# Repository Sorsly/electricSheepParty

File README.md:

# esp
Our senior design project, Electronic Sheep Party.
## Steps to Run
* Turn on LAN (Make sure all bots are configured to connect)
* Set up camera above the bots
* power cycle each bot and wait for the green light to turn off
* run `putilov getIP`, wait
* run `putilov run`, select y
* Launch your two seprate game front ends
* play game

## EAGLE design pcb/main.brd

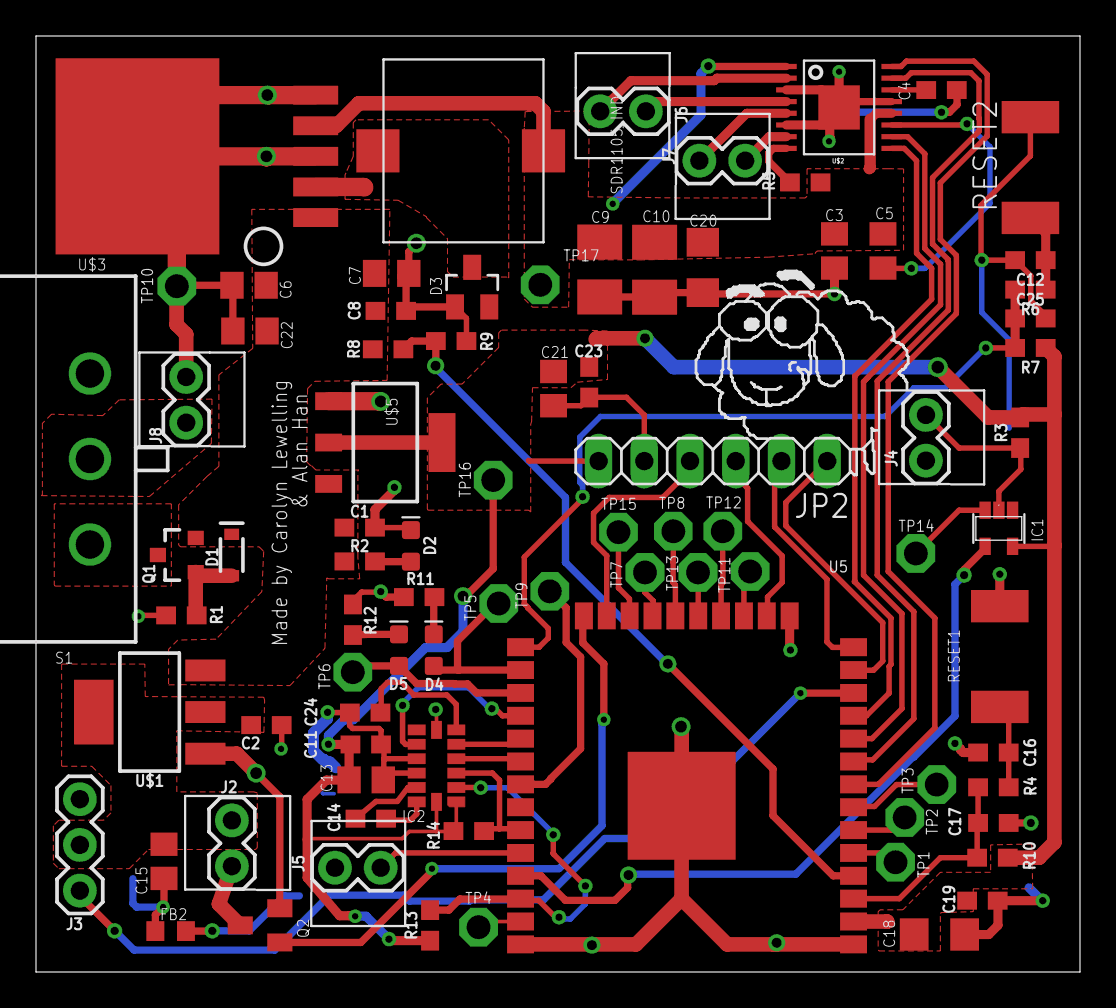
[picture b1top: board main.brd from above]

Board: 2 copper layers, 58.0 x 52.0 mm, 85 parts (0 on the bottom side), 60 nets.

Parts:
C1, C2, C8, C11, C23: 0.1uF; 0603
C3, C5, C7, C13, C15, C21, C22: 10uF; C0805
C4: 2.2uF; C0603
C6: 22uF; C0805
C9, C10: 220uF; B/3528-21R
C12, C16, C17, C25: 1nF; 0603
C14: 0.22uF; 0603
C18, C20: 100uF; C1206
C19: 1uF; 0603
C24: 4.7uF; 0603
D1: 250mA/100V; SOD-323
D2: LED-0603
D3: BAT54; SOT23
D4: red; LED-0603
D5: green; LED-0603
FB2: R0603
FRAME1, FRAME2: FRAME-LETTERNO_PACKAGE; DUMMY
IC1: NC7SZ14M5X; SOT23-5
IC2: LSM303DLHC; LGA-14
J2, J4, J5, J8: 1X02
J3: 455-1750-1-ND; 1X03
J6: M1 connector; 1X02
J7: M2 connector; 1X02
JP2: 1X06
Q1: 2.5A/30V/105mΩ; SOT23-3
Q2: SOT23
R1: 100k; 0603
R2, R11, R12: 330; 0603
R3: 8.2k; 0603
R4, R6, R7, R10: 470; 0603
R5, R13, R14: 10k; 0603
R8: 2k; 0603
R9: 1k; 0603
RESET1, RESET2: S2; SW_2512
S1: L102021ML04Q
TP1, TP2, TP3, TP4, TP5, TP6, TP7, TP8, TP9, TP10, TP11, TP12, TP13, TP14, TP15, TP16, TP17: TPPAD1-13; P1-13
U5: ESP-WROOM-32
U$1: AZ1117E; SOT223
U$2: DRV8833C; HTSSOP-16
U$3: AP1506; TO263-5
U$4: SDR1105_IND; SDR1105
U$5: SC1202-3.3V; SOT-223

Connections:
1/3_BAT: R8.1, R9.2, U5.4
3V3: C11.1, C13.1, C18.1, C19.1, C21.1, C23.1, IC1.5, IC2.1, IC2.14, JP2.6, R3.2, R7.1, R10.1, R13.1, R14.1, TP16.TP, U5.2, U$5.2, U$5.TAB
3V3M: C3.1, C5.1, C9.+, C10.+, C20.1, R5.2, TP17.TP, U$2.1, U$2.12, U$3.4, U$4.P$2
5V: C2.1, C15.2, J2.2, J3.2, U$1.2, U$1.4
6V: C1.1, C6.1, C7.1, C8.1, C22.1, D1.C, Q1.2, R2.2, R8.2, U$1.3, U$3.1, U$5.3
6V_RAW: J8.1, S1.P$2
ADC_PHOTO: IC1.2, J4.2, R3.1
AGND: C1.2, C2.2, C3.2, C4.2, C6.2, C7.2, C8.2, C9.-, C10.-, C15.1, C20.2, C22.2, D2.C, D3.1, FB2.1, J3.3, J8.2, Q2.2, R1.1, R9.1, TP10.TP, U$1.1, U$2.3, U$2.6, U$2.13, U$2.17, U$3.3, U$3.5, U$3.6, U$5.1
DAT_RDY: IC2.9, U5.28
EN: C17.1, R4.2, R10.2, U5.3
GND: C11.2, C12.2, C13.2, C16.2, C17.2, C18.2, C19.2, C21.2, C23.2, C24.2, C25.2, FB2.2, IC1.3, IC2.7, IC2.10, IC2.11, J4.1, J5.1, JP2.5, R11.1, R12.1, RESET1.2, RESET2.2, TP14.TP, U5.1, U5.15, U5.38, U5.GND
INT1: IC2.5, U5.29
INT2: IC2.4, U5.30
IO0: C25.1, R6.2, R7.2, U5.25
M1+: J6.2, U$2.2
M1-: J6.1, U$2.4
M2+: J7.2, U$2.7
M2-: J7.1, U$2.5
unnamed: D1.A, Q1.1, R1.2
unnamed: D2.A, R2.1
unnamed: Q1.3, S1.P$3
unnamed: TP1.TP, U5.5
unnamed: TP2.TP, U5.6
unnamed: C12.1, R6.1, RESET2.1
unnamed: D3.3, U$3.2, U$4.P$1
unnamed: C4.1, U$2.14
unnamed: C5.2, U$2.11
unnamed: J2.1, Q2.3
unnamed: C16.1, R4.1, RESET1.1
unnamed: R5.1, U$2.8
unnamed: TP3.TP, U5.7
unnamed: TP8.TP, U5.20
unnamed: D4.A, TP5.TP, U5.26
unnamed: TP7.TP, U5.21
unnamed: TP15.TP, U5.22
unnamed: D5.A, TP6.TP, U5.27
unnamed: TP11.TP, U5.17
unnamed: TP12.TP, U5.18
unnamed: TP13.TP, U5.19
unnamed: TP9.TP, U5.31
unnamed: TP4.TP, U5.37
unnamed: D4.C, R11.2
unnamed: D5.C, R12.2
unnamed: C14.2, IC2.13
unnamed: C14.1, IC2.12
unnamed: C24.1, IC2.6
PHOTO: IC1.4, U5.35
PWM_LASER: Q2.1, U5.24
PWM_LED: J5.2, U5.34
PWM_M1A: U5.8, U$2.16
PWM_M1B: U5.9, U$2.15
PWM_M2A: U5.11, U$2.9
PWM_M2B: U5.10, U$2.10
PWM_SERVO: J3.1, U5.12
SCL: IC2.2, R13.2, U5.36
SDA: IC2.3, R14.2, U5.33
TCK: JP2.3, U5.16
TDI: JP2.2, U5.14
TDO: JP2.4, U5.23
TMS: JP2.1, U5.13

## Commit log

2017-12-16 add gitignore + cvstuff
2017-12-16 adding cv install
2017-12-16 made and added some documentations
2017-12-23 UDP communication to bot working
2017-12-23 added move function
2018-01-10 adding devkitc sechematic
2018-01-12 stuff
2018-01-18 Build system working
2018-01-18 adding findip script
2018-01-21 added eagle files (sch and lbr)
2018-01-23 added H-bridge
2018-01-23 added more parts, found some parts, updated BOM with more info, reorganized schematic
2018-01-24 finished hbridge and buck converter
    created part for inductor, figured out values for buck converter caps,
    and wired hbridge
2018-01-24 updated hbridge
2018-01-24 added IMU
2018-01-26 changed gnd symbol (some weird 3.3v thing was happening) and added esp32
2018-01-27 added in new gnd symbols (doesn't default to 3.3v anymore); added in esp32 library
2018-01-29 Did IMU and most of UART
2018-01-29 initial pathfinder commit
2018-01-29 more progress
2018-01-30 works
2018-01-31 mosfet for laser
2018-01-31 wired up almost all of esp's peripherals
2018-01-31 updated project file (may have dropped electricSheepParty.lbr accidentally)
2018-02-02 progress
2018-02-02 message
2018-02-02 added putilov
2018-02-02 removing
2018-02-06 more esp pins and isolating grounds
2018-02-07 added schmitt trigger
2018-02-07 finished schematic (draft1)
2018-02-07 JTAG on Clion works
2018-02-07 putilov flashes correctlly
2018-02-08 layout done! (minus sheep image)
    Still need to add sheep and check with tolerances of wherever we fab at,
    but otherwise done!!!!
2018-02-09 added sheep
2018-02-10 fixed silkscreen (tPlace, tNames, tValues)
2018-02-14 added gerbers (oshPark.zip is the one that actually got sent to fab)
2018-02-14 built structure for control algorithm
2018-02-14 renaiming things
2018-02-21 mechanical (solidworks) files moved to repo
2018-02-21 began turret assm redesign, resized turret, added new cuts for: sg90 mount point, wires
2018-02-22 more mech stuff
2018-02-22 turret redesign done
2018-02-23 ui game
2018-02-24 finished battery cap
2018-02-25 command struct sent to bots
2018-02-25 completely finished assembly
    some bugs noticed:
    -wheel assembly has weird references to Assm1 or something like that
    -turret axis mate doesn't play well with other mates
2018-02-25 BOT COMMUNICATION WORKS BITCH, IM JUST AN IDIDOT
2018-02-25 datastructure commmunication working
2018-02-25 commenting + turret controlledover udp
2018-02-26 multiselect
2018-02-26 added colors and finished constraining final model; organized schematic
2018-02-27 fixes to battery holder, screw post adjustments for DC motor
2018-02-28 sch pdf generated
2018-02-28 the other pdf too
2018-03-04 converted battery holder to be detachable cantilevers (ie functional); (hopefully) toleranced turret bottom properly, need to confirm then will tolerance mid and top section (only need to tolerance p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
2018-03-07 all turret adjustments should be good, potentially need to shrink turret to fit within wheel clearance; made rest of body parts detacheable cantilevers
2018-03-08 batteryCant_01mm is actually a good pressfit when printed on T3 Land Factory in conjunction with female parts
2018-03-08 solidworks garbage collection
2018-03-09 editted part layouts. changed pins for uart
2018-03-10 communication
2018-03-11 guess I changed things?
2018-03-12 body is print ready with all fasteners
2018-03-12 CCCP ->Frontend comm
2018-03-13 CCCP->frontend dataparsing+ botmovement
2018-03-13 updating gitignore
2018-03-13 cleaning up clutter
2018-03-13 bringing in old working tracker
2018-03-14 hotfixes
2018-03-15 board JTAG programming working
2018-03-16 Frontend communication fully working
2018-03-16 comminting working frontend
2018-03-16 ok like i know this isnt the best practice but cut me some slack I have a couple branches going on
2018-03-17 periperals working
2018-03-19 camera to CCCP coded (untested)
2018-03-19 gofmt
2018-03-19 wheel fix
2018-03-19 misc
2018-03-20 fix for bodyTop turret wire slots
2018-03-20 changed IDing to hash tables
2018-03-20 in system software bot, camera, CCCP working
2018-03-21 fixes for rev2
    fixed mounting holes, connector overlap, added 6th pin for jtag,
    isolated 3rd switch pin, and added push button for IO0
2018-03-21 moved sheepy
2018-03-21 cable space fix
    The bottom of the body *will* need to be cut more to take advantage of the cable space fix
2018-03-21 extended hole body
    to complement the last commit
2018-03-21 camera holder
2018-03-21 camera name
2018-03-21 i2c comm updates + small putilov updates
2018-03-21 breaking frontend tasks into bot controls
2018-03-21 changing from duty cycle control to relative position control
2018-03-21 sending relative position to the bots
2018-03-22 turret fixed for electrical things; camera fixed and printed
2018-03-22 Peripherals are now controllable thorugh libraries
2018-03-23 movement of turrets working
2018-03-23 some transform scaling
2018-03-23 moved cccp main functions
2018-03-24 new camera holder with 3 attachment points, new pcbHolder for pcb rev2
2018-03-26 i2c tests
2018-03-26 commenting
2018-03-27 bot is being controlled
2018-03-28 Latest
    Latest
2018-03-28 triangle
2018-03-29 adding in the less bullshit bullshit
2018-03-31 calibration step added
2018-04-02 unity from allnighter; frontWeightContainer created; added motor model from grabcad; began omniwheel
2018-04-02 excluded .epf
2018-04-02 finished omniwheel w/ appropriate mods to pcbHolder
2018-04-03 move function rev. 2
2018-04-03 adding CV orientation
2018-04-03 added twiddles to command struct
2018-04-03 adding sdkconfig
2018-04-03 move rev 3
2018-04-03 adding makefile
2018-04-03 adding ota
2018-04-03 move compiled
2018-04-03 modifying putilov to check things
2018-04-04 modded bodyTop for dual extrusion CV; designed omniWheel; misc commits
2018-04-04 bodyTop M600 gcode mod
    removed useless .amf file
2018-04-04 increased cv pattern depth to 0.5mm; added omni ball stl; modded turret top for vertical LED
2018-04-04 Unity update
    locate position on enemy
2018-04-04 cv orientation working
2018-04-05 bot tries to move to the center
2018-04-05 movement integration in progress
2018-04-05 changing dtheta direction
2018-04-05 adjusting des_angle
2018-04-06 finished designing mk4 turret
2018-04-06 fixed quadfin tolerance, led recess, gun recess
2018-04-07 reverting unity
2018-04-07 movement to pos works
2018-04-08 updating unity version
2018-04-08 lots of tiny fixes for the turret to make it work proper; also managed to tweak settings for omni so TPU actually prints properly
2018-04-08 webgl working
2018-04-08 webgl working (again?)
2018-04-08 some toher unity stuff
2018-04-08 omni will use 1.75 filament for core
2018-04-08 can't remember; probably tolerancing
2018-04-08 removing javascript files
2018-04-08 move april-8
2018-04-09 move april-8 2
2018-04-09 made a lot of changes to body for mk3.5 (though I'm not renamign directrories for that); this is in prep for the new turret; also need to modify turret so bolts come in from top not bottom (too diffi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
2018-04-09 made bolt changes to turret mk4 and enlarged turret if I didn't already
2018-04-10 added all the backups and the new things too
2018-04-10 moar chassis compatiblity; split into 2 sectinos almost done; added slots to sides; created hooks for sides; had to fix front weight contain
2018-04-10 DONNEEEE; chassis should be compatible with new turret; new cv top too
2018-04-10 Health count floating above each bot
2018-04-10 working
2018-04-10 rev 2 board
    gerbers and such for second version of board
2018-04-11 unity "working"
2018-04-11 full commit
2018-04-11 something unity something
2018-04-11 Revert "something unity something"
    This reverts commit d66bcf1b36cb134142201bbd8334769e846ef7dd.
2018-04-11 working but jank
2018-04-11 move with small corrections
2018-04-11 working translational
2018-04-12 updated controls
2018-04-12 reduced z variance correction distance from 1mm to 0.2mm
2018-04-12 move with stops
2018-04-12 double pid working
2018-04-12 revert to working
2018-04-12 carolyn working
2018-04-12 controls working
2018-04-12 working?
2018-04-12 pathehad updateding
2018-04-13 paths are overridden
2018-04-13 fine tunes
2018-04-13 CCCP sends pid constants
2018-04-13 designed camera stabilizer (39mm); designed new batteryHolder; updated bodyTopTurret
2018-04-14 getting ota working
2018-04-14 ota working
2018-04-15 battery stuff; bodyTopTurret fix
2018-04-16 small changes
2018-04-16 integrating space bar firing
2018-04-16 added frontend verification to start with 2
2018-04-16 adding initial commit for banch of multibot
2018-04-17 all the unity stuff charles has bene doing; new photo resistor adapter, fixed led cover
2018-04-18 serve on all addresses
2018-04-21 added 3 bots a side
2018-04-22 multiple bots
2018-04-22 communicate with carolyn
2018-04-23 makes requests to carolyn
2018-04-23 bot returns to field after leaving
2018-04-23 changed health to uint8
2018-04-23 omni wheel changes (not really a wheel anymore mk3.5); manufacturing fixes for turretGun and turretGround (apparently we were modeling off the wrong fin (Tower Pro vs FITEC)
2018-04-23 minor change to pcbHolder
2018-04-23 stabilizerClip from 39mm to 37mm, added clip feature; some updated gcode
2018-04-23 multiple ips handled
2018-04-24 added new layer to turret to fix bulge caused by fin screw
2018-04-24 working with caraolyns frontend
2018-04-24 commiting new unity
2018-04-24 turrettracking
2018-04-24 turret tracking working
2018-04-24 making bot want to move closer
2018-04-25 bots burst fire
2018-04-25 removing log iport
2018-04-25 fixing health bug
2018-04-26 added some programming code
2018-04-27 erer
2018-04-27 werk werk werk
2018-04-27 sleep deprived shit
2018-04-27 blah
2018-04-27 adding ip
2018-04-28 Spark challenge commit
2018-05-03 updating readme

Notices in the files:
parts and their libraries:
SparkFun-Aesthetics: Licensing: Creative Commons ShareAlike 4.0 International - https://creativecommons.org/licenses/by-sa/4.0
